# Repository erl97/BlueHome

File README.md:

# BlueHome Project

Zweite Version der Node#2 Platine

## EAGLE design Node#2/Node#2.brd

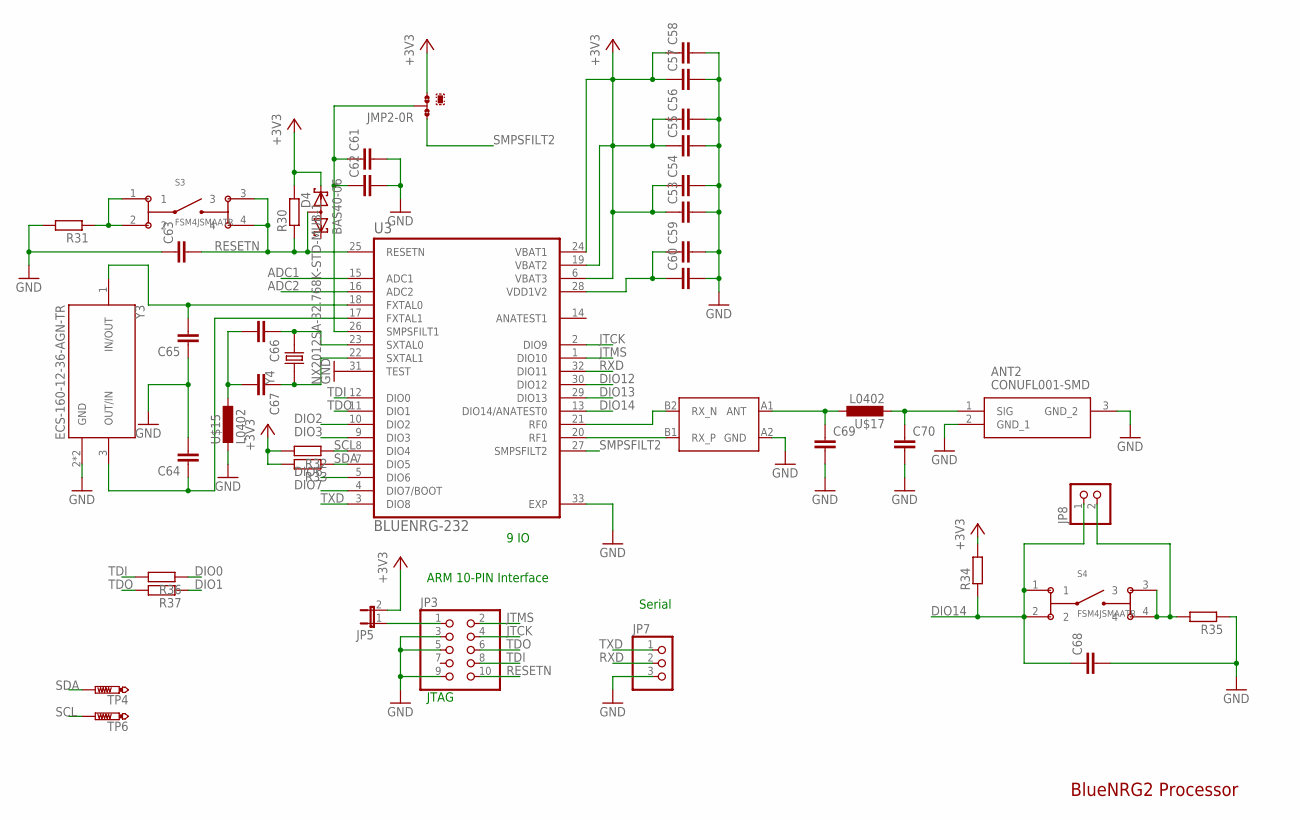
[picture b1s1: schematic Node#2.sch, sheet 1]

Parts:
ANT2: CONUFL001-SMD
C53, C54, C55, C56, C57, C58, C59, C60, C61, C62: C-EUC0805K; C0805K
C63, C64, C65, C66, C67, C68: C-EUC0805; C0805
C69, C70: C-EUC0402; C0402
D4: BAS40-06; SOT23
JMP2: 0R-JUMPA; A0R-JMP
JP3: PINHD-2X5; 2X05
JP5: JP1E; JP1
JP7: PINHD-1X3; 1X03
JP8: PINHD-1X2; 1X02
R30, R31, R32, R33, R36, R37: R-EU_R0805; R0805
R34, R35: R-EU_R1210; R1210
S3, S4: FSM4JSMAATR; SW_FSM4JSMAATR
TP4, TP6: PTR1TP20R; TP20R
U3: BLUENRG-232; QFN50P500X500X100-33T345N
U$15, U$17: L0402; R0402
U$16: BALF-NRG-01D3; FLIPCHIP
Y3: ECS-160-12-36-AGN-TR; XTAL_ECS-160-12-36-AGN-TR
Y4: NX2012SA-32.768K-STD-MUB-1; XTAL_NX2012SA-32.768K-STD-MUB-1

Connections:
+3V3: C53.1, C54.1, C55.1, C56.1, C57.1, C58.1, D4.2 (K2), JMP2.3, JP5.2, R30.2, R32.2, R33.2, R34.2, U3.6 (VBAT3), U3.19 (VBAT2), U3.24 (VBAT1); also elsewhere on the board
ADC1: U3.15 (ADC1); also elsewhere on the board
ADC2: U3.16 (ADC2); also elsewhere on the board
DIO0: R36.1; also elsewhere on the board
DIO1: R37.1; also elsewhere on the board
DIO2: U3.10 (DIO2); also elsewhere on the board
DIO3: U3.9 (DIO3); also elsewhere on the board
DIO6: U3.5 (DIO6); also elsewhere on the board
DIO7: U3.4 (DIO7/BOOT); also elsewhere on the board
DIO12: U3.30 (DIO12); also elsewhere on the board
DIO13: U3.29 (DIO13); also elsewhere on the board
DIO14: C68.1, JP8.1, R34.1, S4.1, S4.2, U3.13 (DIO14/ANATEST0)
GND: ANT2.2 (GND_1), ANT2.3 (GND_2), C53.2, C54.2, C55.2, C56.2, C57.2, C58.2, C59.2, C60.2, C61.2, C62.2, C63.1, C64.2, C65.1, C68.2, C69.2, C70.2, JP3.3, JP3.5, JP3.9, JP7.3, R31.2, R35.1, U3.31 (TEST), U3.33 (EXP), U$15.2, U$16.A2 (GND), Y3.2 (GND), Y3.4 (GND); also elsewhere on the board
JTCK: JP3.4, U3.2 (DIO9)
JTMS: JP3.2, U3.1 (DIO10)
unnamed: C59.1, C60.1, U3.28 (VDD1V2)
unnamed: C61.1, C62.1, JMP2.2, U3.26 (SMPSFILT1)
unnamed: R31.1, S3.1, S3.2
unnamed: C64.1, U3.17 (FXTAL1), Y3.3 (OUT/IN)
unnamed: C65.2, U3.18 (FXTAL0), Y3.1 (IN/OUT)
unnamed: C66.2, C67.2, U$15.1
unnamed: C66.1, U3.23 (SXTAL0), Y4.2
unnamed: C67.1, U3.22 (SXTAL1), Y4.1
unnamed: C69.1, U$16.A1 (ANT), U$17.1
unnamed: ANT2.1 (SIG), C70.1, U$17.2
unnamed: JP3.1, JP5.1
unnamed: JP8.2, R35.2, S4.3, S4.4
unnamed: U3.20 (RF1), U$16.B1 (RX_P)
unnamed: U3.21 (RF0), U$16.B2 (RX_N)
RESETN: C63.2, D4.3 (AA), JP3.10, R30.1, S3.3, S3.4, U3.25 (RESETN); also elsewhere on the board
RXD: JP7.2, U3.32 (DIO11)
SCL: R32.1, TP6.TP, U3.8 (DIO4); also elsewhere on the board
SDA: R33.1, TP4.TP, U3.7 (DIO5); also elsewhere on the board
SMPSFILT2: JMP2.1, U3.27 (SMPSFILT2)
TDI: JP3.8, R36.2, U3.12 (DIO0)
TDO: JP3.6, R37.2, U3.11 (DIO1)
TXD: JP7.1, U3.3 (DIO8)

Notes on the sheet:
JTAG
ARM 10-PIN Interface
9 IO
Serial
BlueNRG2 Processor

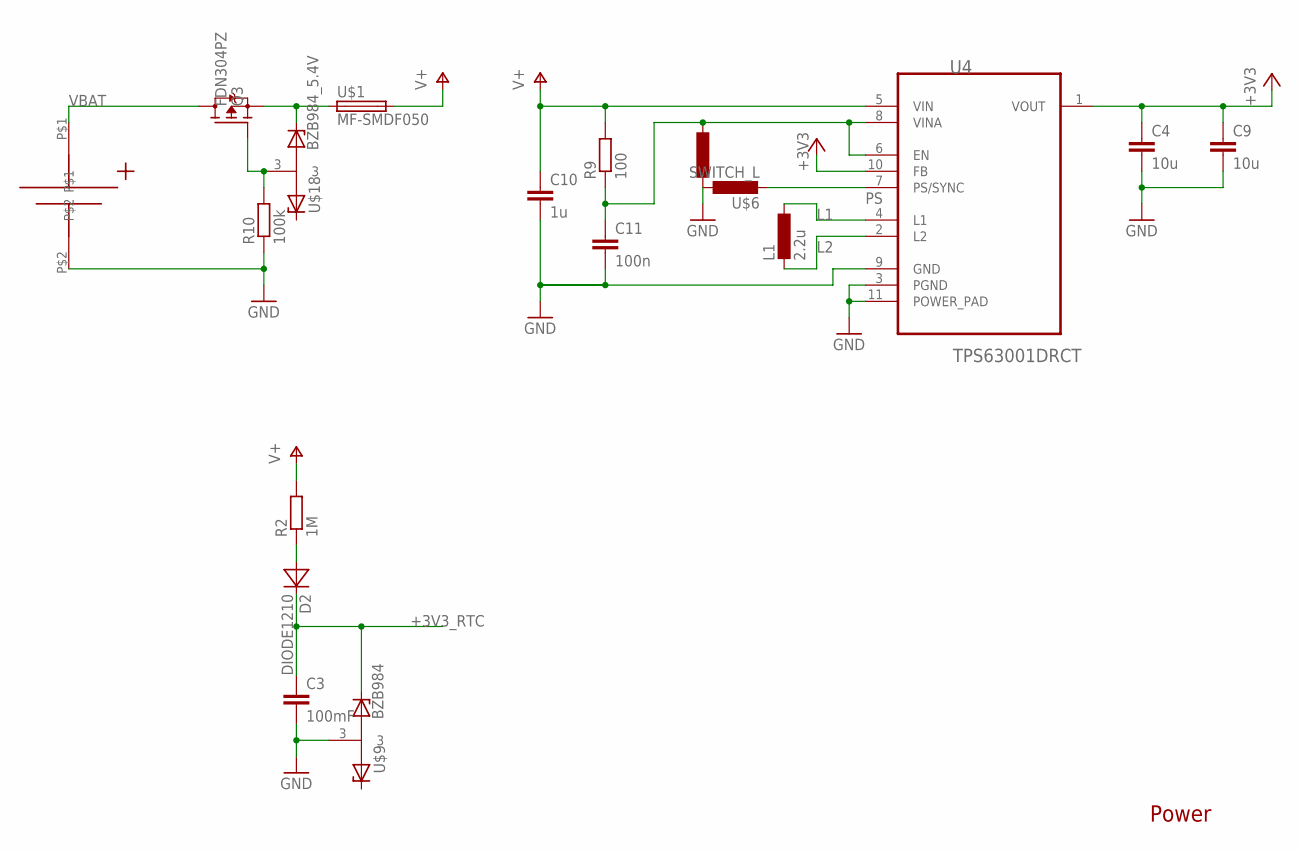
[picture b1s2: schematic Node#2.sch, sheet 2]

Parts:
C3: 100mF; C050-055X075
C4, C9: 10u; C0805
C10: 1u; C0805
C11: 100n; C0805
D2: DIODE1210; C1210
L1: 2.2u; L5038P
Q3: FDN304PZ; SOT23
R2: 1M; R0805
R9: 100; R0805
R10: 100k; R0805
U4: TPS63001DRCT; SON50P300X300X100-11N
U$1: MF-SMDF050
U$6: SWITCH_L; R0805_2
U$9: BZB984; SOT95P230X110-3N
U$10: BATTER_HOLDER; BATTERY_HOLDER
U$18: BZB984_5.4V; SOT95P230X110-3N

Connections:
+3V3: C4.1, C9.1, U4.1 (VOUT), U4.10 (FB); also elsewhere on the board
+3V3_RTC: C3.1, D2.2 (C), U$9.2; also elsewhere on the board
GND: C3.2, C4.2, C9.2, C10.2, C11.2, R10.1, U4.3 (PGND), U4.9 (GND), U4.11 (POWER_PAD), U$6.2 (1), U$9.3, U$10.P$2; also elsewhere on the board
L1: L1.1, U4.4 (L1)
L2: L1.2, U4.2 (L2)
unnamed: D2.1 (A), R2.1
unnamed: Q3.2S (S), U$1.1, U$18.2
unnamed: C11.1, R9.1, U4.6 (EN), U4.8 (VINA), U$6.3
unnamed: Q3.1G (G), R10.2, U$18.3
PS: U4.7 (PS/SYNC), U$6.1 (2)
V+: C10.1, R2.2, R9.2, U4.5 (VIN), U$1.2; also elsewhere on the board
VBAT: Q3.3D (D), U$10.P$1

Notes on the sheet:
Power

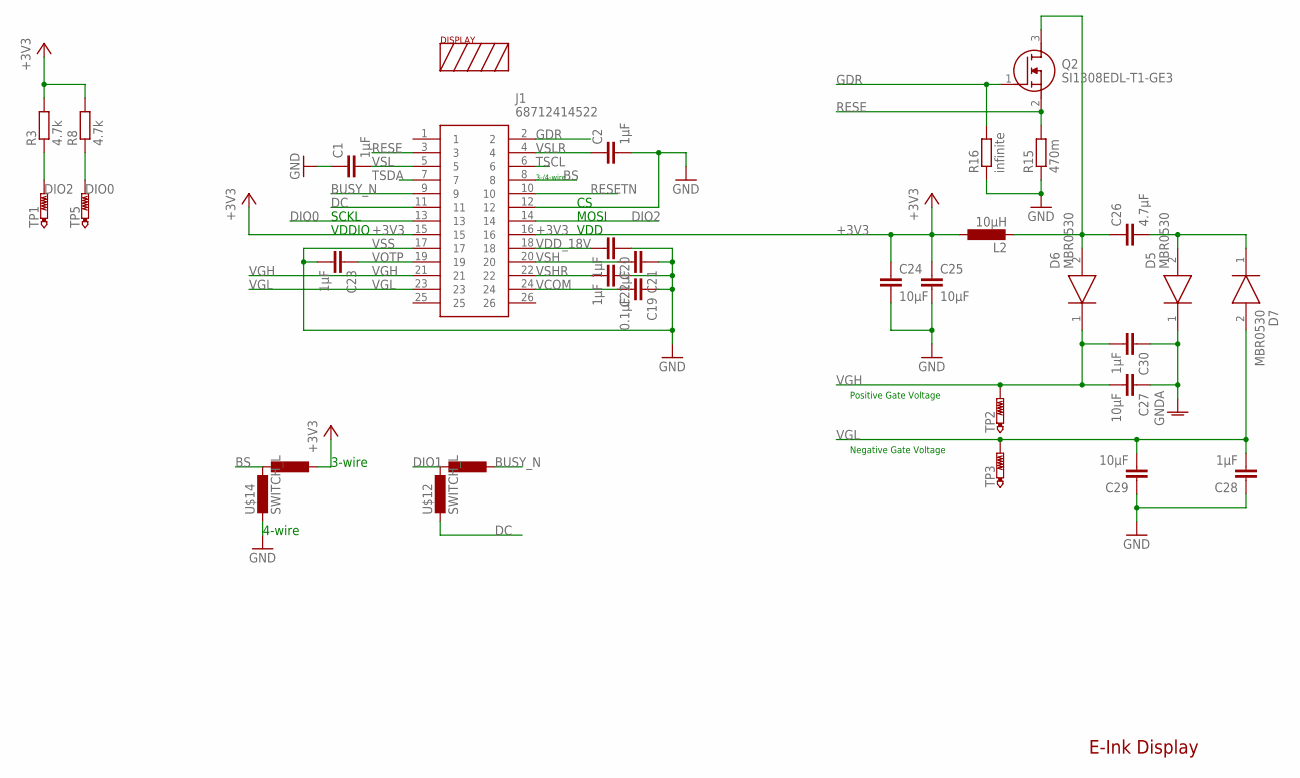
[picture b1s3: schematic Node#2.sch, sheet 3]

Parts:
C1, C2, C20, C21, C22, C23, C28, C30: 1µF; C0805
C19: 0.1µF; C0805
C24, C25, C27, C29: 10µF; C0805
C26: 4.7µF; C0805
D5, D6, D7: MBR0530; SOD3716X135N
J1: 68712414522
L2: 10µH; L5038P
Q2: SI1308EDL-T1-GE3; SOT65P210X110-3N
R3, R8: 4.7k; R0805
R15: 470m; R0805
R16: infinite; R0805
TP1, TP2, TP3, TP5: PTR1TP20R; TP20R
U$11: DISPLAY
U$12, U$14: SWITCH_L; R0805_2

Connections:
+3V3: C24.1, C25.1, J1.15, J1.16, L2.1, R3.2, R8.2, U$14.3; also elsewhere on the board
BS: J1.8, U$14.2 (1)
BUSY_N: J1.9, U$12.3
DC: J1.11, U$12.1 (2)
DIO0: J1.13, R8.1, TP5.TP; also elsewhere on the board
DIO1: U$12.2 (1); also elsewhere on the board
DIO2: J1.14, R3.1, TP1.TP; also elsewhere on the board
GDR: J1.2, Q2.1 (G), R16.2
GND: C1.1, C2.2, C24.2, C25.2, C27.1, C28.1, C29.1, C30.1, D5.1 (K), J1.12, R15.1, R16.1, U$14.1 (2); also elsewhere on the board
unnamed: C26.1, D6.2 (A), L2.2, Q2.3 (D)
unnamed: C26.2, D5.2 (A), D7.1 (K)
RESE: J1.3, Q2.2 (S), R15.2
RESETN: J1.10; also elsewhere on the board
TSCL: J1.6
TSDA: J1.7
VCOM: C19.2, J1.24
VDD_18V: C20.2, J1.18
VGH: C27.2, C30.2, D6.1 (K), J1.21, TP2.TP
VGL: C28.2, C29.2, D7.2 (A), J1.23, TP3.TP
VOTP: C23.1, J1.19
VSH: C21.2, J1.20
VSHR: C22.2, J1.22
VSL: C1.2, J1.5
VSLR: C2.1, J1.4
VSS: C19.1, C20.1, C21.1, C22.1, C23.2, J1.17

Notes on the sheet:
3-/4-wire
VDDIO
VDD
Positive Gate Voltage
Negative Gate Voltage
E-Ink Display
SCKL
MOSI
4-wire
3-wire

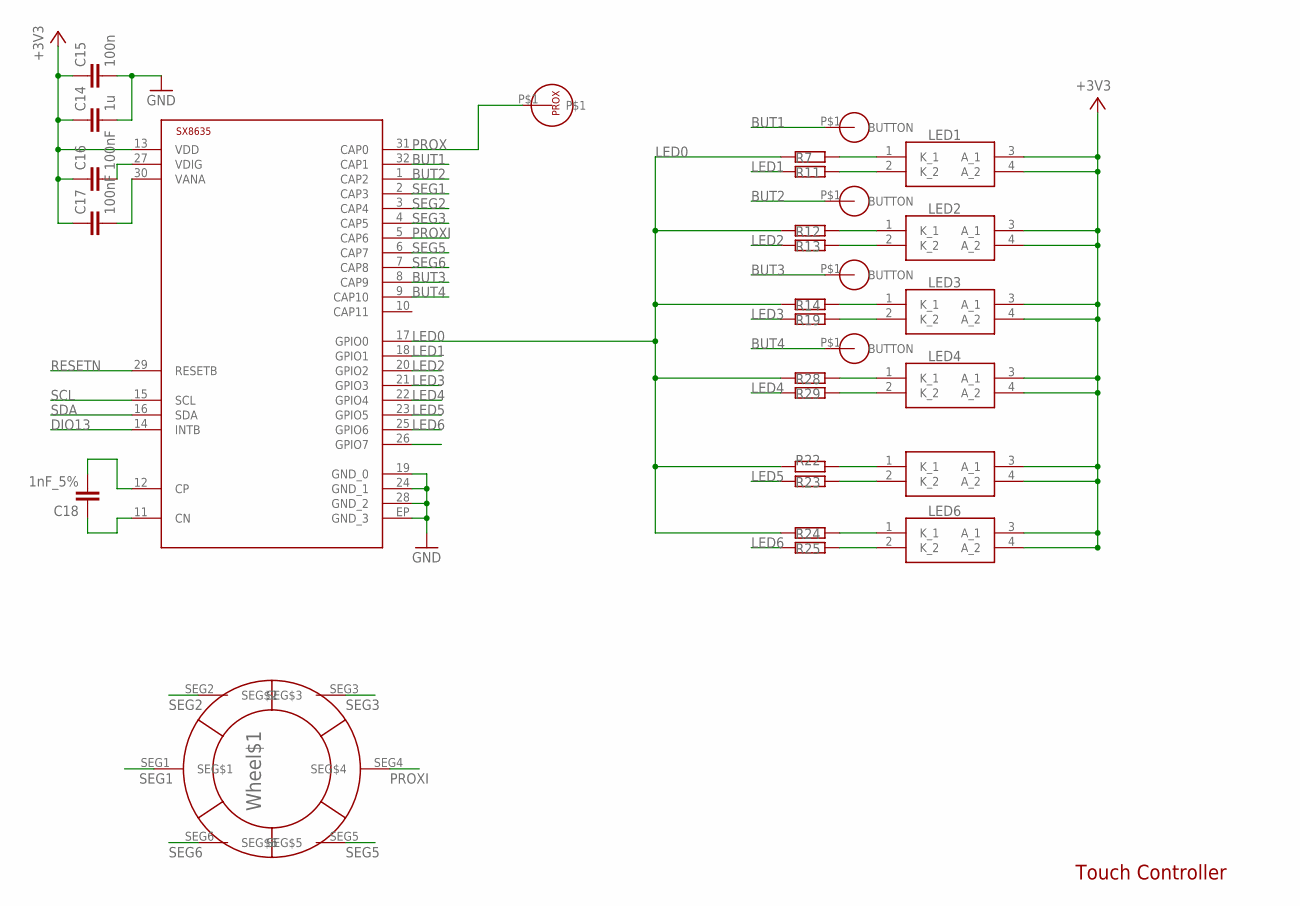
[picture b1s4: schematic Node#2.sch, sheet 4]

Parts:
C14: 1u; C0805
C15: 100n; C0805
C16, C17: 100nF; C0805
C18: 1nF_5%; C0805
LED1, LED2, LED3, LED4, LED5, LED6: 156125YV73000
PROXI: PROXIMITY
R7, R11, R12, R13, R14, R19, R22, R23, R24, R25, R28, R29: R-EU_R0805; R0805
U$2: SX8635; QFN-32
U$3, U$4, U$5, U$13: TOUCH_BUTTON
U$19: WHEEL6

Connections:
+3V3: C14.1, C15.1, C16.1, C17.1, LED1.3 (A_1), LED1.4 (A_2), LED2.3 (A_1), LED2.4 (A_2), LED3.3 (A_1), LED3.4 (A_2), LED4.3 (A_1), LED4.4 (A_2), LED5.3 (A_1), LED5.4 (A_2), LED6.3 (A_1), LED6.4 (A_2), U$2.13 (VDD); also elsewhere on the board
BUT1: U$2.32 (CAP1), U$3.P$1
BUT2: U$2.1 (CAP2), U$4.P$1
BUT3: U$2.8 (CAP9), U$5.P$1
BUT4: U$2.9 (CAP10), U$13.P$1
DIO13: U$2.14 (INTB); also elsewhere on the board
GND: C14.2, C15.2, U$2.19 (GND_0), U$2.24 (GND_1), U$2.28 (GND_2), U$2.EP (GND_3); also elsewhere on the board
LED0: R7.1, R12.1, R14.1, R22.1, R24.1, R28.1, U$2.17 (GPIO0)
LED1: R11.1, U$2.18 (GPIO1)
LED2: R13.1, U$2.20 (GPIO2)
LED3: R19.1, U$2.21 (GPIO3)
LED4: R29.1, U$2.22 (GPIO4)
LED5: R23.1, U$2.23 (GPIO5)
LED6: R25.1, U$2.25 (GPIO6)
unnamed: LED1.1 (K_1), R7.2
unnamed: LED1.2 (K_2), R11.2
unnamed: LED3.1 (K_1), R14.2
unnamed: LED3.2 (K_2), R19.2
unnamed: LED5.1 (K_1), R22.2
unnamed: LED5.2 (K_2), R23.2
unnamed: C16.2, U$2.27 (VDIG)
unnamed: C17.2, U$2.30 (VANA)
unnamed: C18.2, U$2.12 (CP)
unnamed: C18.1, U$2.11 (CN)
unnamed: LED2.1 (K_1), R12.2
unnamed: LED2.2 (K_2), R13.2
unnamed: LED4.1 (K_1), R28.2
unnamed: LED4.2 (K_2), R29.2
unnamed: LED6.1 (K_1), R24.2
unnamed: LED6.2 (K_2), R25.2
PROX: PROXI.P$1, U$2.31 (CAP0)
PROXI: U$2.5 (CAP6), U$19.SEG4 (SEG$4)
RESETN: U$2.29 (RESETB); also elsewhere on the board
SCL: U$2.15 (SCL); also elsewhere on the board
SDA: U$2.16 (SDA); also elsewhere on the board
SEG1: U$2.2 (CAP3), U$19.SEG1 (SEG$1)
SEG2: U$2.3 (CAP4), U$19.SEG2 (SEG$2)
SEG3: U$2.4 (CAP5), U$19.SEG3 (SEG$3)
SEG5: U$2.6 (CAP7), U$19.SEG5 (SEG$5)
SEG6: U$2.7 (CAP8), U$19.SEG6 (SEG$6)

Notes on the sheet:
Touch Controller

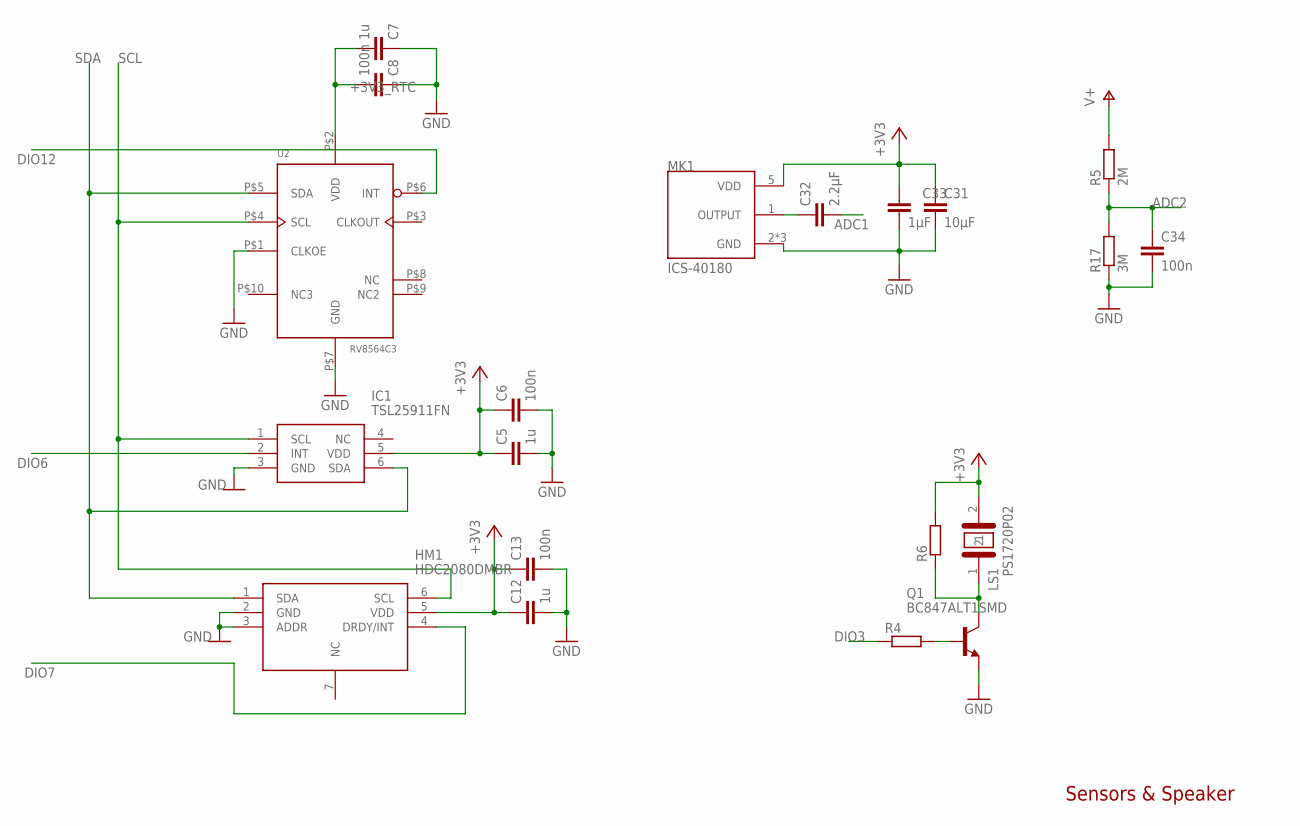
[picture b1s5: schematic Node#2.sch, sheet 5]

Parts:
C5, C7, C12: 1u; C0805
C6, C8, C13, C34: 100n; C0805
C31: 10µF; C0805
C32: 2.2µF; C0805
C33: 1µF; C0805
HM1: HDC2080DMBR; SON100P300X300X80-7N
IC1: TSL25911FN
LS1: PS1720P02; PS17_1
MK1: ICS-40180; MIC_ICS-40180
Q1: BC847ALT1SMD; SOT23
R4, R6: R-EU_R0805; R0805
R5: 2M; R0805
R17: 3M; R0805
U2: RV8564C3; RTC-C3

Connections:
+3V3: C5.1, C6.1, C12.1, C13.1, C31.1, C33.1, HM1.5 (VDD), IC1.5 (VDD), LS1.2, MK1.5 (VDD), R6.2; also elsewhere on the board
+3V3_RTC: C7.2, C8.2, U2.P$2 (VDD); also elsewhere on the board
ADC1: C32.2; also elsewhere on the board
ADC2: C34.1, R5.1, R17.2; also elsewhere on the board
DIO3: R4.1; also elsewhere on the board
DIO6: IC1.2 (INT); also elsewhere on the board
DIO7: HM1.4 (DRDY/INT); also elsewhere on the board
DIO12: U2.P$6 (INT); also elsewhere on the board
GND: C5.2, C6.2, C7.1, C8.1, C12.2, C13.2, C31.2, C33.2, C34.2, HM1.2 (GND), HM1.3 (ADDR), IC1.3 (GND), MK1.2 (GND), MK1.3 (GND), MK1.4 (GND), Q1.2 (E), R17.1, U2.P$1 (CLKOE), U2.P$7 (GND); also elsewhere on the board
unnamed: C32.1, MK1.1 (OUTPUT)
unnamed: LS1.1, Q1.3 (C), R6.1
unnamed: Q1.1 (B), R4.2
SCL: HM1.6 (SCL), IC1.1 (SCL), U2.P$4 (SCL); also elsewhere on the board
SDA: HM1.1 (SDA), IC1.6 (SDA), U2.P$5 (SDA); also elsewhere on the board
V+: R5.2; also elsewhere on the board

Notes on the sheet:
Sensors & Speaker

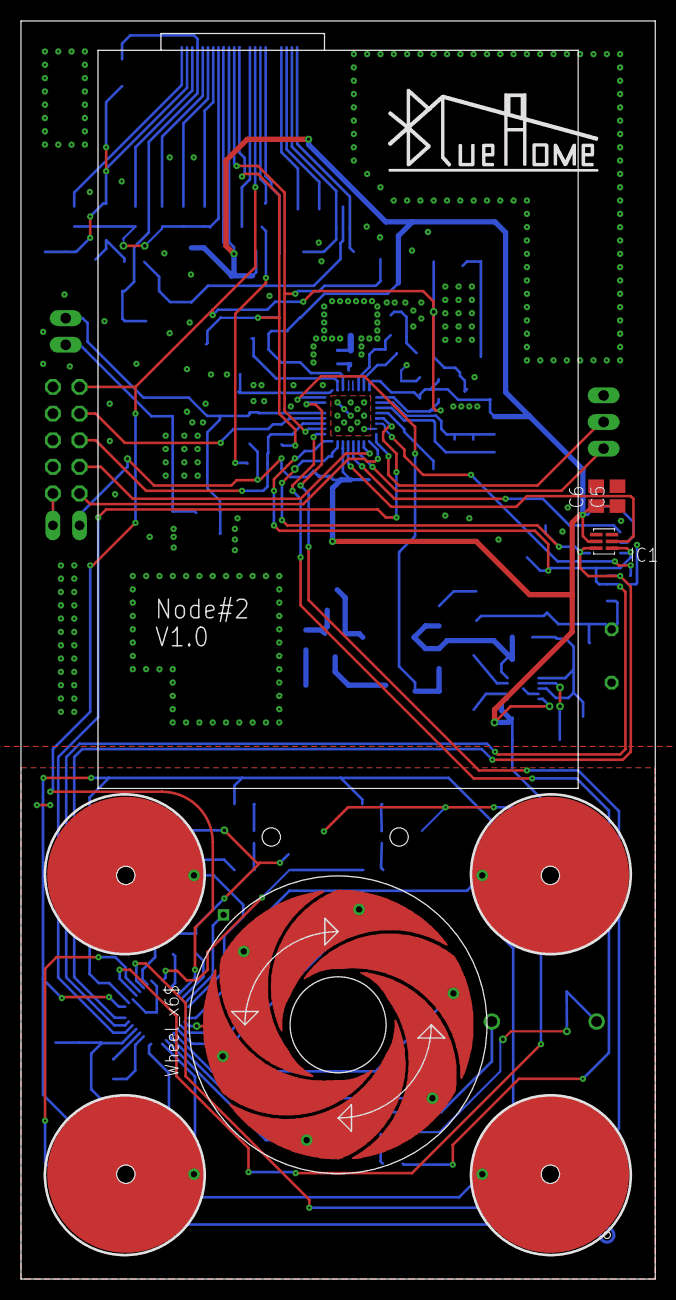
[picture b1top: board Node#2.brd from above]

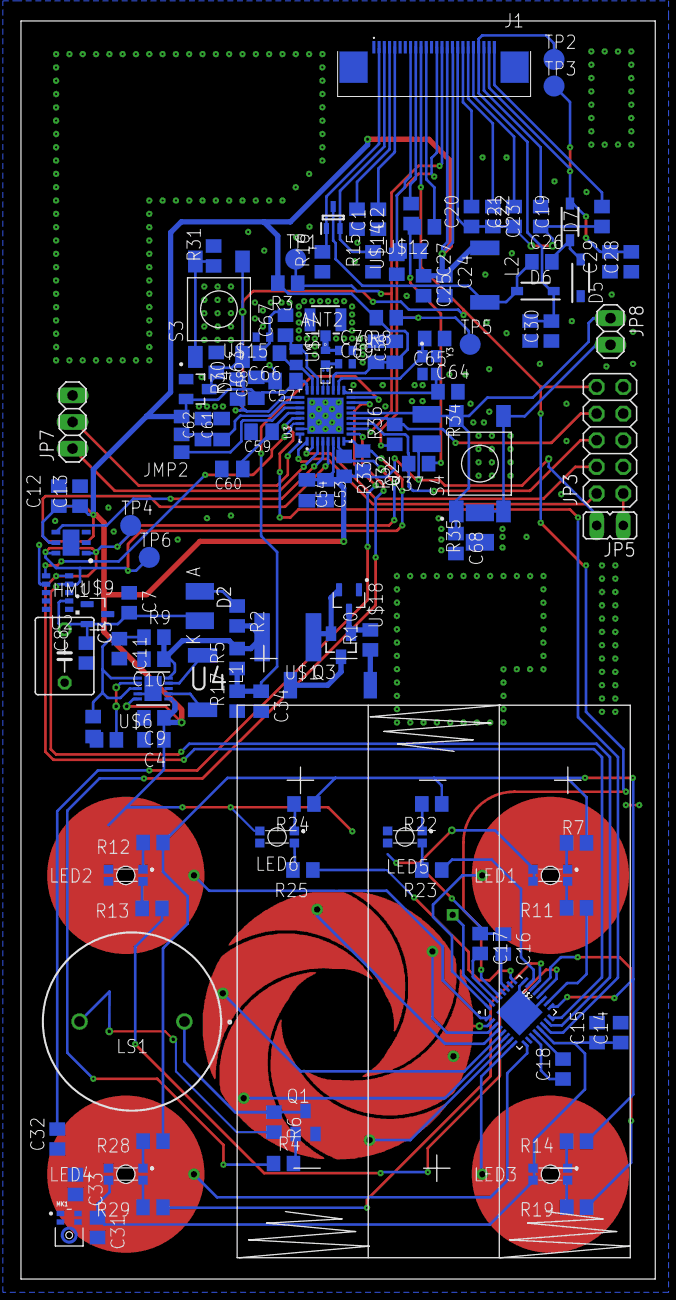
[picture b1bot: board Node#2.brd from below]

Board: 2 copper layers, 60.5 x 120.0 mm, 141 parts (131 on the bottom side), 101 nets.

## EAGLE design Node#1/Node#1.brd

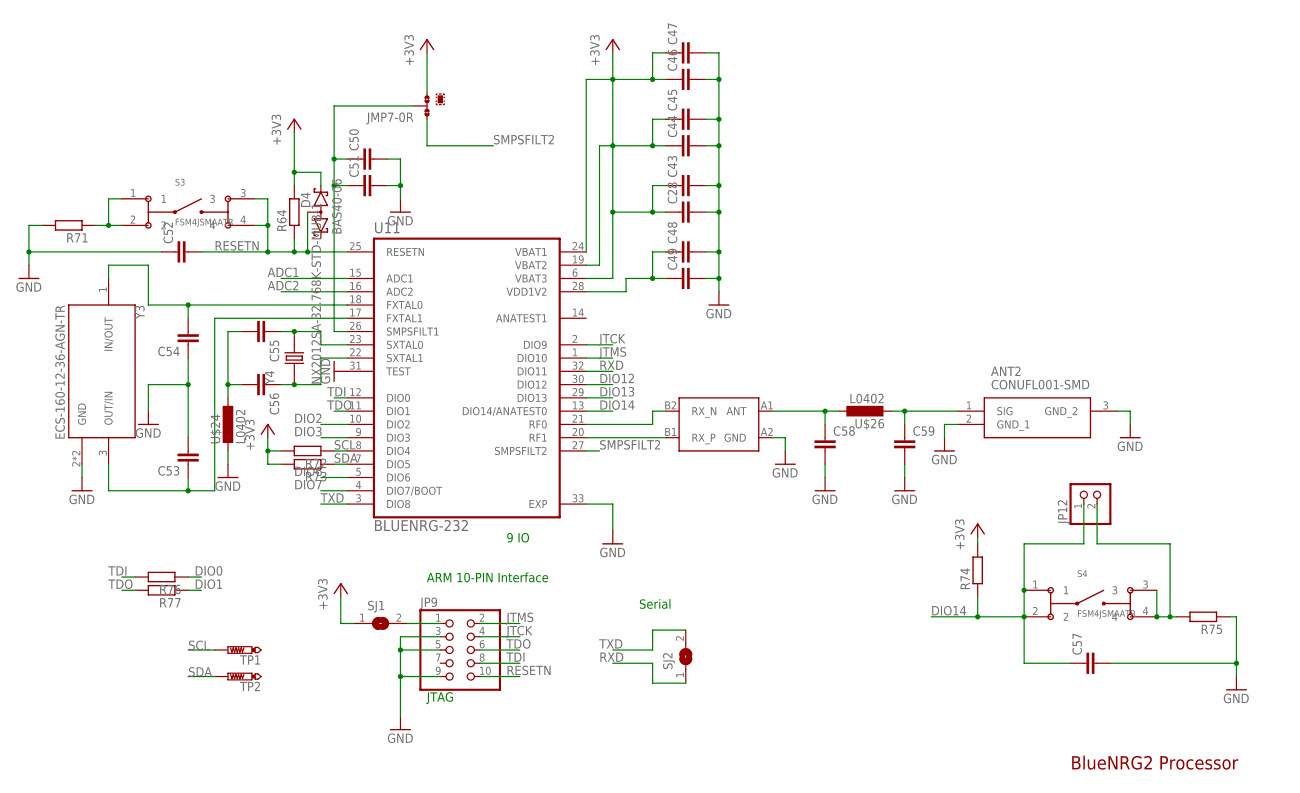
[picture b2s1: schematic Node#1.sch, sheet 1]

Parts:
ANT2: CONUFL001-SMD
C28, C43, C44, C45, C46, C47, C48, C49, C50, C51: C-EUC0805K; C0805K
C52, C53, C54, C55, C56, C57: C-EUC0805; C0805
C58, C59: C-EUC0402; C0402
D4: BAS40-06; SOT23
JMP7: 0R-JUMPA; A0R-JMP
JP9: PINHD-2X5; 2X05
JP12: PINHD-1X2; 1X02
R64, R71, R72, R73, R76, R77: R-EU_R0805; R0805
R74, R75: R-EU_M0805; M0805
S3, S4: FSM4JSMAATR; SW_FSM4JSMAATR
SJ1, SJ2: SJ
TP1, TP2: PTR1TP20R; TP20R
U11: BLUENRG-232; QFN50P500X500X100-33T345N
U$24, U$26: L0402; R0402
U$25: BALF-NRG-01D3; FLIPCHIP
Y3: ECS-160-12-36-AGN-TR; XTAL_ECS-160-12-36-AGN-TR
Y4: NX2012SA-32.768K-STD-MUB-1; XTAL_NX2012SA-32.768K-STD-MUB-1

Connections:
+3V3: C28.1, C43.1, C44.1, C45.1, C46.1, C47.1, D4.2 (K2), JMP7.3, R64.2, R72.2, R73.2, R74.2, SJ1.1, U11.6 (VBAT3), U11.19 (VBAT2), U11.24 (VBAT1); also elsewhere on the board
ADC1: U11.15 (ADC1)
ADC2: U11.16 (ADC2); also elsewhere on the board
DIO0: R76.1
DIO1: R77.1
DIO2: U11.10 (DIO2); also elsewhere on the board
DIO3: U11.9 (DIO3); also elsewhere on the board
DIO6: U11.5 (DIO6); also elsewhere on the board
DIO7: U11.4 (DIO7/BOOT); also elsewhere on the board
DIO12: U11.30 (DIO12); also elsewhere on the board
DIO13: U11.29 (DIO13); also elsewhere on the board
DIO14: C57.1, JP12.1, R74.1, S4.1, S4.2, U11.13 (DIO14/ANATEST0)
GND: ANT2.2 (GND_1), ANT2.3 (GND_2), C28.2, C43.2, C44.2, C45.2, C46.2, C47.2, C48.2, C49.2, C50.2, C51.2, C52.1, C53.2, C54.1, C57.2, C58.2, C59.2, JP9.3, JP9.5, JP9.9, R71.2, R75.1, U11.31 (TEST), U11.33 (EXP), U$24.2, U$25.A2 (GND), Y3.2 (GND), Y3.4 (GND); also elsewhere on the board
JTCK: JP9.4, U11.2 (DIO9)
JTMS: JP9.2, U11.1 (DIO10)
unnamed: C48.1, C49.1, U11.28 (VDD1V2)
unnamed: C50.1, C51.1, JMP7.2, U11.26 (SMPSFILT1)
unnamed: R71.1, S3.1, S3.2
unnamed: C53.1, U11.17 (FXTAL1), Y3.3 (OUT/IN)
unnamed: C54.2, U11.18 (FXTAL0), Y3.1 (IN/OUT)
unnamed: C55.2, C56.2, U$24.1
unnamed: C55.1, U11.23 (SXTAL0), Y4.2
unnamed: C56.1, U11.22 (SXTAL1), Y4.1
unnamed: C58.1, U$25.A1 (ANT), U$26.1
unnamed: ANT2.1 (SIG), C59.1, U$26.2
unnamed: JP9.1, SJ1.2
unnamed: JP12.2, R75.2, S4.3, S4.4
unnamed: U11.20 (RF1), U$25.B1 (RX_P)
unnamed: U11.21 (RF0), U$25.B2 (RX_N)
RESETN: C52.2, D4.3 (AA), JP9.10, R64.1, S3.3, S3.4, U11.25 (RESETN); also elsewhere on the board
RXD: SJ2.1, U11.32 (DIO11)
SCL: R72.1, TP1.TP, U11.8 (DIO4); also elsewhere on the board
SDA: R73.1, TP2.TP, U11.7 (DIO5); also elsewhere on the board
SMPSFILT2: JMP7.1, U11.27 (SMPSFILT2)
TDI: JP9.8, R76.2, U11.12 (DIO0)
TDO: JP9.6, R77.2, U11.11 (DIO1)
TXD: SJ2.2, U11.3 (DIO8)

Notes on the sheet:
BlueNRG2 Processor
JTAG
ARM 10-PIN Interface
9 IO
Serial

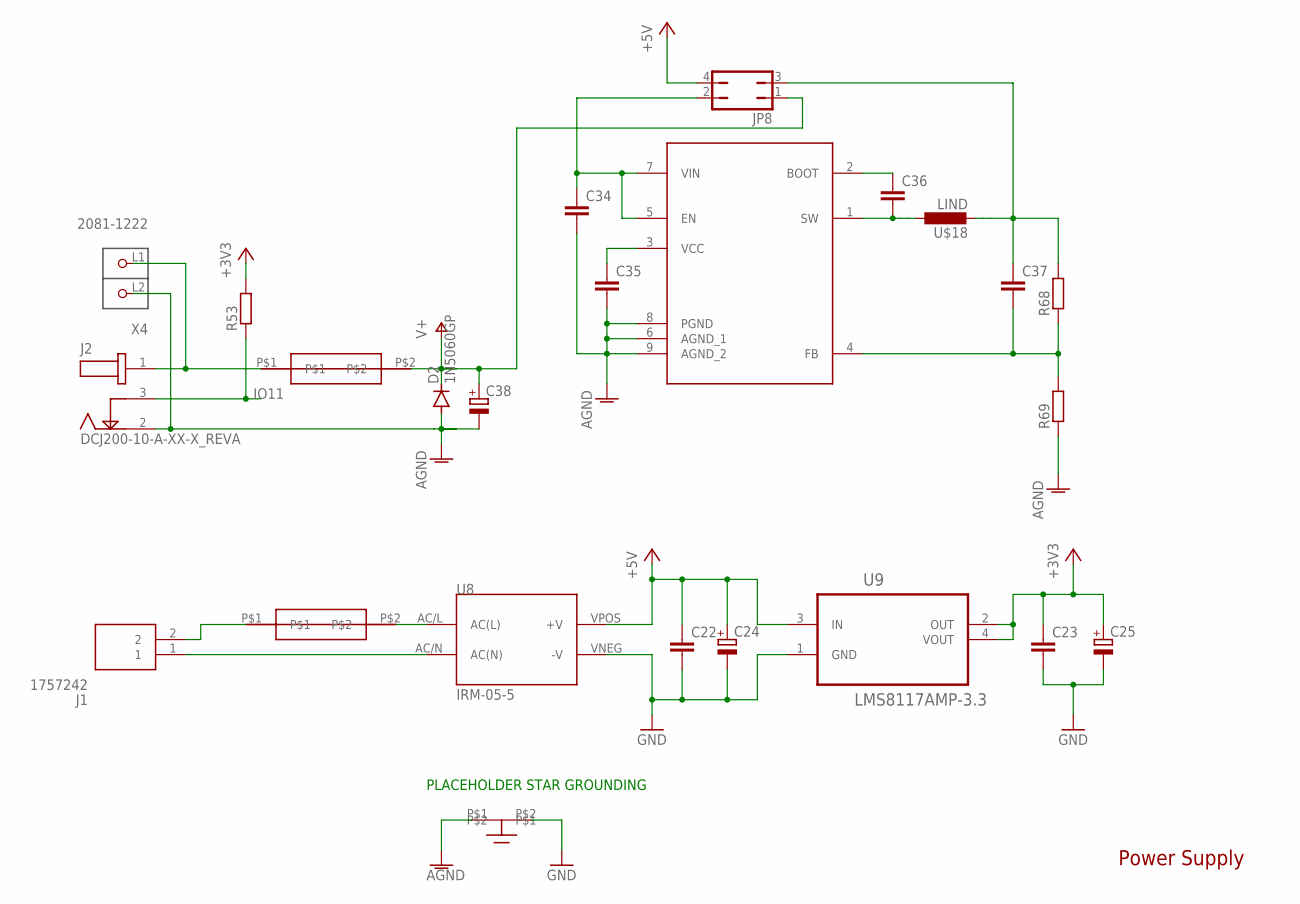
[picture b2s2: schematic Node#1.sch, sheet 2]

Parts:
C22, C23, C34, C35, C36, C37: C-EUC0805; C0805
C24, C25: CPOL-EUSMCC; SMC_C
C38: CPOL-EU150CLZ-1010; 150CLZ-1010
D2: 1N5060GP; DO15-12
J1: 1757242; SHDR2W120P0X508_1X2_1208X1200X
J2: DCJ200-10-A-XX-X_REVA; GCT_DCJ200-10-A-XX-X_REVA
JP8: JP2Q
R53, R68, R69: R-EU_R0805; R0805
U8: IRM-05-5; CONV_IRM-05-5
U9: LMS8117AMP-3.3; SOT230P696X180-4N
U$9, U$20: RND170-00004
U$18: LIND; INDM1200X1200X1000N
U$21: LM23610; SOIC127P600X170-8N
U$23: STAR_GROUND
X4: 2081-1222; P-2081-1222

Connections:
+3V3: C23.1, C25.+, R53.2, U9.2 (OUT), U9.4 (VOUT); also elsewhere on the board
+5V: C22.1, C24.+, JP8.4, U8.VPOS (+V), U9.3 (IN); also elsewhere on the board
AGND: C34.2, C35.2, C38.-, D2.A, J2.2, R69.1, U$21.6 (AGND_1), U$21.8 (PGND), U$21.9 (AGND_2), U$23.P$1, X4.L2 (P2); also elsewhere on the board
GND: C22.2, C23.2, C24.-, C25.-, U8.VNEG (-V), U9.1 (GND), U$23.P$2; also elsewhere on the board
IO11: J2.3, R53.1; also elsewhere on the board
unnamed: J2.1, U$20.P$1, X4.L1 (P1)
unnamed: C34.1, JP8.2, U$21.5 (EN), U$21.7 (VIN)
unnamed: C35.1, U$21.3 (VCC)
unnamed: U8.AC/L (AC(L)), U$9.P$2
unnamed: C36.1, U$21.2 (BOOT)
unnamed: J1.1, U8.AC/N (AC(N))
unnamed: J1.2, U$9.P$1
unnamed: C36.2, U$18.1, U$21.1 (SW)
unnamed: C37.2, R68.1, R69.2, U$21.4 (FB)
unnamed: C37.1, JP8.3, R68.2, U$18.2
V+: C38.+, D2.C, JP8.1, U$20.P$2; also elsewhere on the board

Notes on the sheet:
PLACEHOLDER STAR GROUNDING
Power Supply

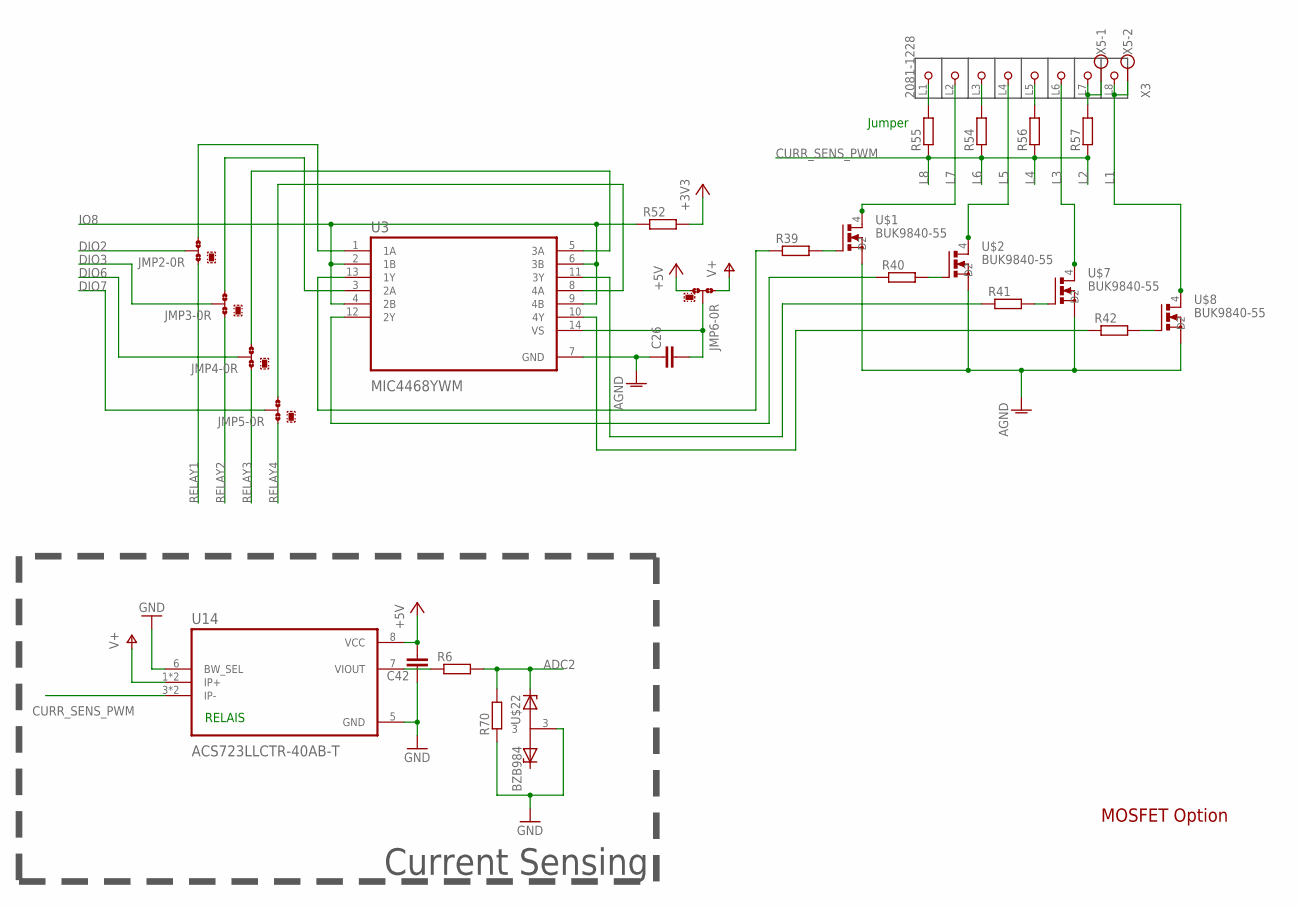
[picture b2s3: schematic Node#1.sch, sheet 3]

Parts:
C26, C42: C-EUC0805; C0805
JMP2, JMP3, JMP4, JMP5, JMP6: 0R-JUMPA; A0R-JMP
R6, R39, R40, R41, R42, R52, R70: R-EU_M0805; M0805
R54, R55, R56, R57: R-EU_R1210; R1210
U3: MIC4468YWM; SOIC127P1030X265-16N
U14: ACS723LLCTR-40AB-T; SOIC127P600X175-8N
U$1, U$2, U$7, U$8: BUK9840-55; SOT230P696X180-4N
U$22: BZB984; SOT95P230X110-3N
X3: 2081-1228; P-2081-1228
X5: W237-102

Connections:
+3V3: R52.2; also elsewhere on the board
+5V: C42.2, JMP6.3, U14.8 (VCC); also elsewhere on the board
ADC2: R6.2, R70.2, U$22.1; also elsewhere on the board
AGND: C26.1, U3.7 (GND), U$1.3 (S), U$2.3 (S), U$7.3 (S), U$8.3 (S); also elsewhere on the board
CURR_SENS_PWM: R54.1, R55.1, R56.1, R57.1, U14.3 (IP-), U14.4 (IP-)
DIO2: JMP2.2; also elsewhere on the board
DIO3: JMP3.2; also elsewhere on the board
DIO6: JMP4.2; also elsewhere on the board
DIO7: JMP5.2; also elsewhere on the board
GND: C42.1, R70.1, U14.5 (GND), U14.6 (BW_SEL), U$22.3; also elsewhere on the board
IO8: R52.1, U3.2 (1B), U3.4 (2B), U3.6 (3B), U3.9 (4B); also elsewhere on the board
L1: U$8.2 (D), U$8.4 (D2), X3.L8 (P8), X5.2; also elsewhere on the board
L2: R57.2, X3.L7 (P7), X5.1; also elsewhere on the board
L3: U$7.2 (D), U$7.4 (D2), X3.L6 (P6); also elsewhere on the board
L4: R56.2, X3.L5 (P5); also elsewhere on the board
L5: U$2.2 (D), U$2.4 (D2), X3.L4 (P4); also elsewhere on the board
L6: R54.2, X3.L3 (P3); also elsewhere on the board
L7: U$1.2 (D), U$1.4 (D2), X3.L2 (P2); also elsewhere on the board
L8: R55.2, X3.L1 (P1); also elsewhere on the board
unnamed: JMP5.3, U3.8 (4A)
unnamed: R39.1, U3.13 (1Y)
unnamed: JMP2.3, U3.1 (1A)
unnamed: JMP3.3, U3.3 (2A)
unnamed: JMP4.3, U3.5 (3A)
unnamed: R40.1, U3.12 (2Y)
unnamed: R41.1, U3.11 (3Y)
unnamed: R42.1, U3.10 (4Y)
unnamed: R39.2, U$1.1 (G)
unnamed: R40.2, U$2.1 (G)
unnamed: R41.2, U$7.1 (G)
unnamed: R42.2, U$8.1 (G)
unnamed: R6.1, U14.7 (VIOUT)
unnamed: C26.2, JMP6.2, U3.14 (VS)
RELAY1: JMP2.1; also elsewhere on the board
RELAY2: JMP3.1; also elsewhere on the board
RELAY3: JMP4.1; also elsewhere on the board
RELAY4: JMP5.1; also elsewhere on the board
V+: JMP6.1, U14.1 (IP+), U14.2 (IP+); also elsewhere on the board

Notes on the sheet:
MOSFET Option
RELAIS
Current Sensing
Jumper

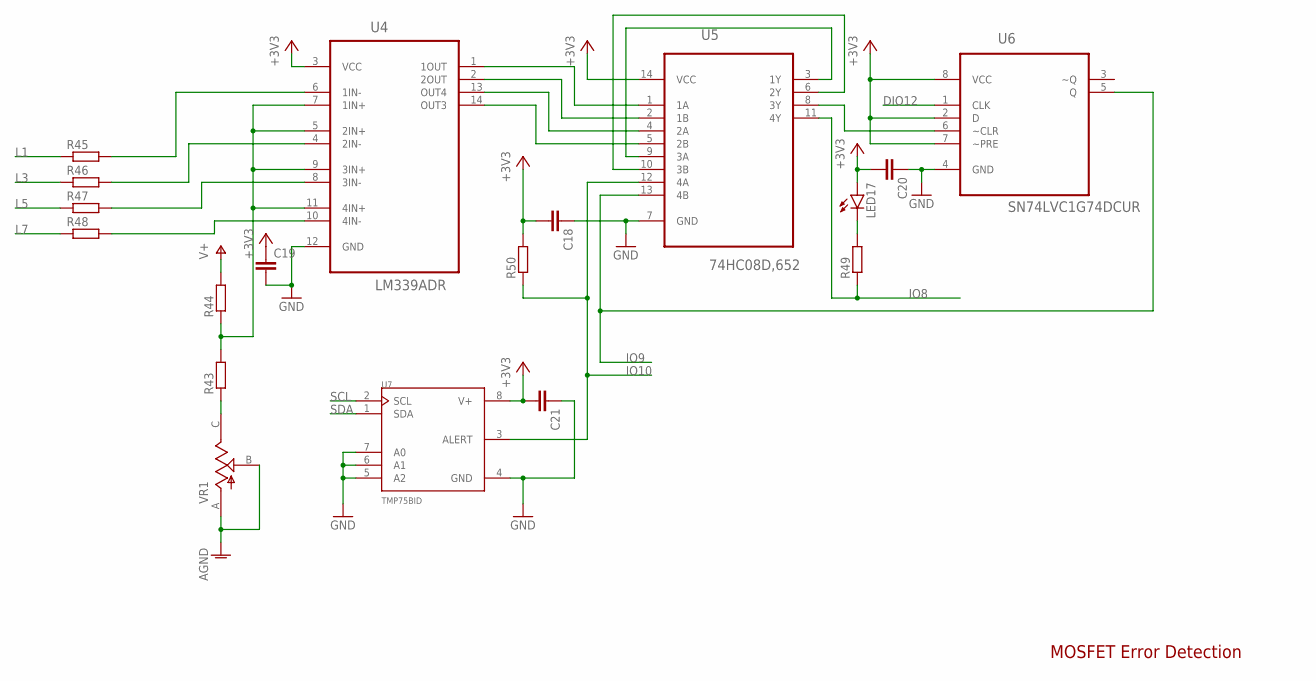
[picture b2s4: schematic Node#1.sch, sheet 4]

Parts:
C18, C19, C20, C21: C-EUC0805; C0805
LED17: LED3MM
R43, R44, R45, R46, R47, R48, R49, R50: R-EU_M0805; M0805
U4: LM339ADR; SOIC127P600X175-14N
U5: 74HC08D,652; SOIC127P600X175-14N
U6: SN74LVC1G74DCUR; SOP50P310X90-8N
U7: TMP75BID; SOIC127P600X175-8N
VR1: TS53YJ103MR10; TRIM_TS53YJ103MR10

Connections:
+3V3: C18.2, C19.1, C20.2, C21.2, LED17.A, R50.2, U4.3 (VCC), U5.14 (VCC), U6.2 (D), U6.7 (~PRE), U6.8 (VCC), U7.8 (V+); also elsewhere on the board
AGND: VR1.A, VR1.B; also elsewhere on the board
DIO12: U6.1 (CLK); also elsewhere on the board
GND: C18.1, C19.2, C20.1, C21.1, U4.12 (GND), U5.7 (GND), U6.4 (GND), U7.4 (GND), U7.5 (A2), U7.6 (A1), U7.7 (A0); also elsewhere on the board
IO8: R49.1, U5.11 (4Y); also elsewhere on the board
IO9: U5.13 (4B), U6.5 (Q); also elsewhere on the board
IO10: R50.1, U5.12 (4A), U7.3 (ALERT); also elsewhere on the board
L1: R45.1; also elsewhere on the board
L3: R46.1; also elsewhere on the board
L5: R47.1; also elsewhere on the board
L7: R48.1; also elsewhere on the board
unnamed: LED17.K (C), R49.2
unnamed: R43.1, VR1.C
unnamed: R43.2, R44.1, U4.5 (2IN+), U4.7 (1IN+), U4.9 (3IN+), U4.11 (4IN+)
unnamed: R45.2, U4.6 (1IN-)
unnamed: U4.1 (1OUT), U5.1 (1A)
unnamed: R48.2, U4.10 (4IN-)
unnamed: R47.2, U4.8 (3IN-)
unnamed: R46.2, U4.4 (2IN-)
unnamed: U4.2 (2OUT), U5.2 (1B)
unnamed: U4.13 (OUT4), U5.4 (2A)
unnamed: U4.14 (OUT3), U5.5 (2B)
unnamed: U5.3 (1Y), U5.9 (3A)
unnamed: U5.6 (2Y), U5.10 (3B)
unnamed: U5.8 (3Y), U6.6 (~CLR)
SCL: U7.2 (SCL); also elsewhere on the board
SDA: U7.1 (SDA); also elsewhere on the board
V+: R44.2; also elsewhere on the board

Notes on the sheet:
MOSFET Error Detection
